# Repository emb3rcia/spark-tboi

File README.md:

# spark-tboi
# Navigation
- [About project](#about-project)
  - [Motivation for the project](#motivation-for-the-project)
  - [Humorous additions](#humorous-additions)
  - [Pin tables](#pin-tables)
  - [Development tools](#development-tools)
  - [Features](#features)
- [Images](#images)
- [License](#license)

# About project

spark-tboi is small-footprint keyboard/macropad with autoclicking capabilities and hot-swappable switches for The Binding of Isaac: Repentance+

## Motivation for the project

spark-debug was created to reduce strain on arms that happens when spam-clicking arrow keys with items such as Spirit Sword or Chocolate Milk

## Humorous additions

I added humorous silkscreen text as this project lacks personality without them in my opinion.

## Pin tables

Pin tables on PCB's silkscreen are named based on IC pins, not on desired connection on it. This means that TX UART pin should be plugged to RX of debugged device and vice versa.

## Usage

spark-tboi can run either only with firmware only or with integration with TBoI via mod that will be made after building the device.

## Directory overview

- 3D file of PCB and case files are available in `/3D`
- KiCad project files are available in `/KiCad Project Files`
- Gerber files are available in `/Gerbers`
- Firmware files are available in `/Firmware`

## Development tools

- KiCad for EDA work
- STM32CubeMX and CLion for firmware
- Fusion Educational Edition for CAD work

## Features

- Small footprint
- Autoclicking capabilities for specific items
- OLED screen

# Images

Schematic

3D viewer top side

3D viewer bottom side

Case assembled

Top plate

Bottom case

# License

## PCB / Schematic License

All files in `/PCB`, `/Schematic` and `/Gerbers` folders and their subsequent subfolders are licensed under the CERN Open Hardware License v2 (Weakly Reciprocal).

See `/Licenses/CERN-OHL.txt` for full terms.

## 3D files, images and documentation License

All files in `/3D`, `/Images` folders and their subsequent subfolders are licensed under the CC-BY 4.0 License.

See `/Licenses/CC-BY-4.0.txt` for full terms

## Software License

All files in `/Firmware` folder and their subsequent subfolders are licensed under the Apache 2.0 License.

See `/Licenses/Apache-2.0.txt` for full terms.

# BOM

|Name                          |Purpose                                                          |Quantity|Total Cost (USD)|Link                                                                                                 |Distributor|
|------------------------------|-----------------------------------------------------------------|--------|----------------|-----------------------------------------------------------------------------------------------------|-----------|
|GRM1555C1H180JA01D            |Capacitors for crystal                                           |2       |0.22            |https://www.tme.eu/pl/details/grm1555c1h180ja01d/kondensatory-mlcc-smd/murata/                       |TME        |
|0603B103K500CT                |Decoupling capacitors for MCU                                    |4       |0.27            |https://www.tme.eu/pl/en/details/0603b103k500ct/mlcc-smd-capacitors/walsin/                          |TME        |
|ABMM2-8.000MHZ-E2-T           |8 MHz oscillator for USB FS                                      |1       |1.03            |https://www.tme.eu/pl/en/details/abmm2-8.000mhz-e2/smd-quartz-generators/abracon/abmm2-8-000mhz-e2-t/|TME        |
|Outemu Kailh CPG151101S11     |Hot-swap switches (i have them from other project)               |15      |0.00            |https://pl.aliexpress.com/item/1005002637150446.html?gatewayAdapt=glo2pol                            |AliExpress |
|Switches and keycaps          |Physical buttons (i have them from hackpad kit and other project)|15      |0.00            |                                                                                                     |HackClub   |
|FOJAN FRC0603J472 TS          |Pull up/down resistors (i have them from other project)          |3       |0.00            |https://www.lcsc.com/product-detail/C2907166.html                                                    |LCSC       |
|Samsung Electro-Mechanics     |10uf decoupling capacitor (i have them from other project)       |1       |0.00            |https://www.lcsc.com/product-detail/C19702.html                                                      |LCSC       |
|HRE CGA0603X7R104K500JT       |100nf decoupling capacitors (i have them from other project)     |2       |0.00            |https://www.lcsc.com/product-detail/C6119867.html                                                    |LCSC       |
|Littelfuse SMBJ5.0A           |TVS diode for vbus (i have it from different project)            |1       |0.00            |https://www.lcsc.com/product-detail/C83333.html                                                      |LSCS       |
|Alps EC11                     |Rotary Encoder leftover from hackpad kit                         |1       |0.00            |                                                                                                     |HackClub   |
|SSD1306                       |OLED 128x32 SSD1306 screen leftover from hackpad kit             |1       |0.00            |                                                                                                     |HackClub   |
|SHOU HAN TYPE-C 16PIN 2MD(073)|USB-C Port (i have it from other project)                        |1       |0.00            |https://www.lcsc.com/product-detail/C2765186.html?s_z=n_C2765186                                     |LCSC       |
|PCB                           |PCB                                                              |5       |32.50           |https://jlcpcb.com                                                                                   |JLCPCB     |
|ST STM32F103C8T7              |MCU                                                              |1       |7.00            |https://www.tme.eu/pl/details/stm32f103c8t7/mikrokontrolery-st/stmicroelectronics/                   |TME        |

© 2026 emb3rcia

Hardware: CERN OHL v2
3D & Images: CC BY 4.0
Firmware: Apache 2.0

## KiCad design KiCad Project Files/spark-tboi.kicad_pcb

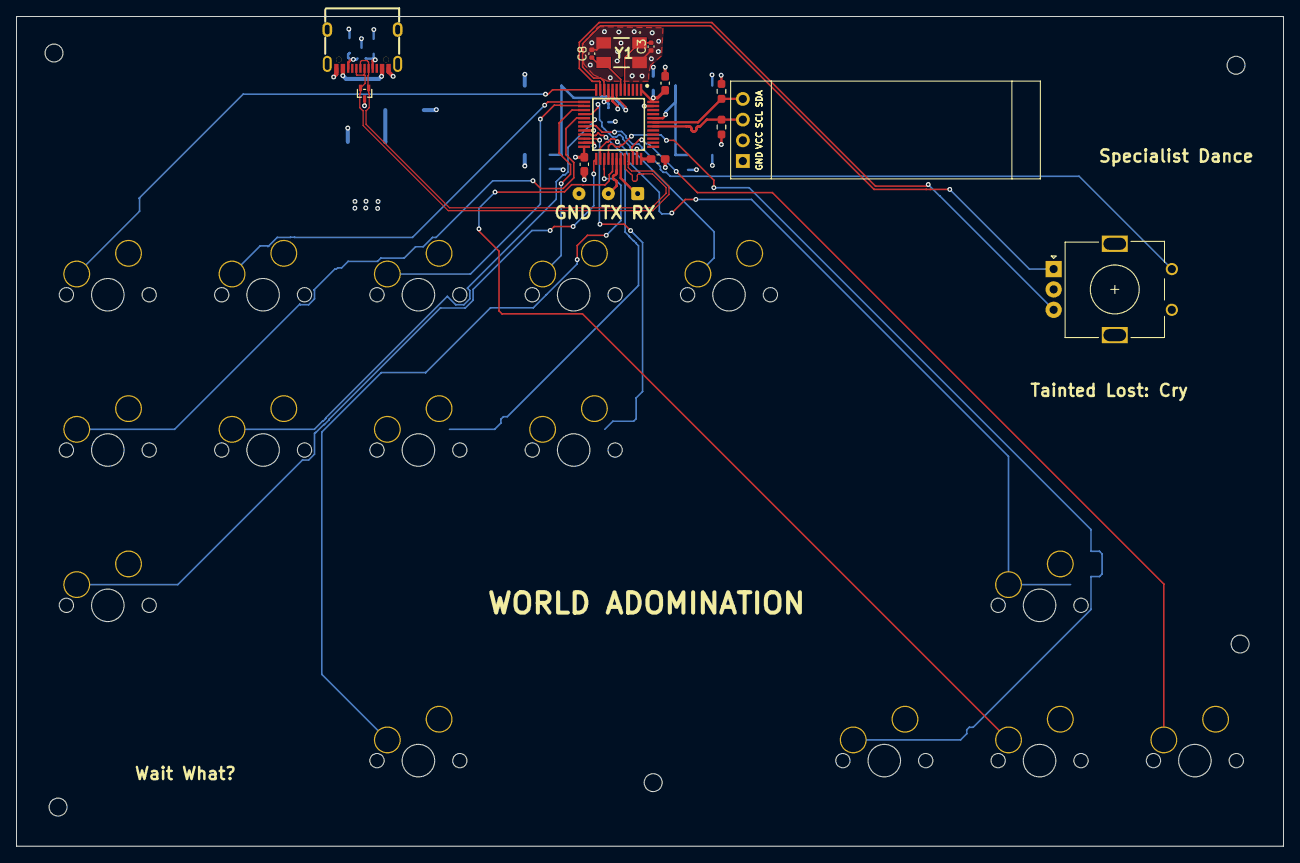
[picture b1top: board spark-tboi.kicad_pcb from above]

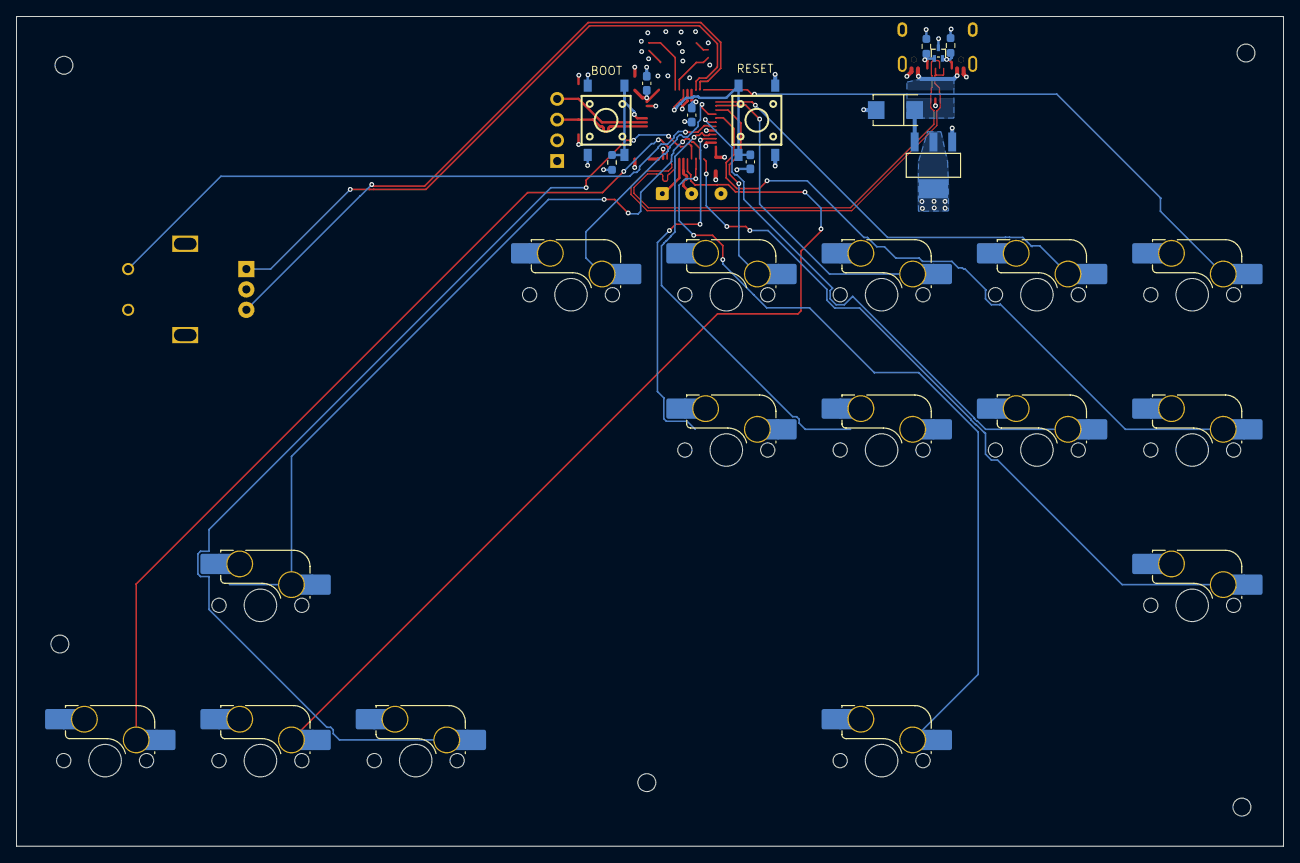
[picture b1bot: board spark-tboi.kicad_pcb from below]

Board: 4 copper layers, 155.4 x 101.8 mm, 40 parts (26 on the bottom side), 32 nets.

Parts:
3V3_LDO1: AMS1117-3.3_C917183; SOT-223-3_L6.7-W3.7-P2.30-LS7.0-BR
BOOT_BUTTON1: TS6643TP 250GF 009; SW-SMD_4P-L6.2-W6.0-P4.50-LS9.0
C1: 4.7uF; C_0603_1608Metric_Pad1.08x0.95mm_HandSolder
C2, C4, C6, C7: 10nF; C_0603_1608Metric_Pad1.08x0.95mm_HandSolder
C3, C8: 18pF; C_0402_1005Metric
C5: 100nF; C_0603_1608Metric_Pad1.08x0.95mm_HandSolder
CC_TVS1: RCLAMP0502BATCT; SC-75-3_L1.6-W0.8-P1.00-LS1.6-BR
CH1, CH2, CH3, CH4, CH5, CH6, CH7, CH8, CH9, CH10, CH11, CH12, CH13, CH14, CH15: KS33_SW_HS; SW_MX_HS_CPG151101S11_1u
DATA_TVS1: RCLAMP0502BATCT; SC-75-3_L1.6-W0.8-P1.00-LS1.6-BR
ENCODER1: RotaryEncoder_Switch; RotaryEncoder_Alps_EC11E_Vertical_H20mm
IC1: STM32F103C8T7; QFP50P900X900X160-48N
NRST_BUTTON1: TS6643TP 250GF 009; SW-SMD_4P-L6.2-W6.0-P4.50-LS9.0
OLED1: Conn_01x04_Pin; SSD1306-0.91-OLED-4pin-128x32
R1, R2, R3: 4.7kOhm; R_0603_1608Metric_Pad0.98x0.95mm_HandSolder
R4, R5: 5.1kOhm; R_0603_1608Metric_Pad0.98x0.95mm_HandSolder
UART1: Conn_01x03_Pin; SolderWire-0.1sqmm_1x03_P3.6mm_D0.4mm_OD1mm
USB1: TYPE-C 16PIN 2MD(073); USB-C-SMD_TYPE-C-6PIN-2MD-073
VBUS_TVS1: SMBJ5.0A_C83333; SMB_L4.6-W3.6-LS5.3-RD
Y1: ABMM2-8.000MHZ-E2-T; ABMM2

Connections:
5V: 3V3_LDO1.3 (VIN), USB1.2 (VBUS), USB1.11 (VBUS), VBUS_TVS1.1
+3.3V: 3V3_LDO1.2 (VOUT), 3V3_LDO1.4 (VOUT), BOOT_BUTTON1.3 (C), BOOT_BUTTON1.4 (D), C1.1, C2.1, C4.1, C6.1, C7.1, IC1.1 (VBAT), IC1.9 (VDDA), IC1.24 (VDD_1), IC1.36 (VDD_2), IC1.48 (VDD_3), OLED1.2, R1.1, R2.1
BOOT0: BOOT_BUTTON1.1 (A), BOOT_BUTTON1.2 (B), IC1.44 (BOOT0), R3.1
CC1: CC_TVS1.1, R5.1, USB1.4 (CC1)
CC2: CC_TVS1.2, R4.1, USB1.10 (CC2)
GND: 3V3_LDO1.1 (GND), C1.2, C2.2, C3.1, C4.2, C5.2, C6.2, C7.2, C8.2, CC_TVS1.3, CH1.2, CH2.2, CH3.2, CH4.2, CH5.2, CH6.2, CH7.2, CH8.2, CH9.2, CH10.2, CH11.2, CH12.2, CH13.2, CH14.2, CH15.2, DATA_TVS1.3, ENCODER1.C, IC1.8 (VSSA), IC1.20 (PB2), IC1.23 (VSS_1), IC1.35 (VSS_2), IC1.47 (VSS_3), NRST_BUTTON1.3 (C), NRST_BUTTON1.4 (D), OLED1.1, R3.2, R4.2, R5.2, UART1.3, USB1.1 (GND), USB1.12 (GND), USB1.13 (SHELL), USB1.14 (SHELL), VBUS_TVS1.2, Y1.2 (GND_1), Y1.4 (GND_2)
NRST: C5.1, IC1.7 (NRST), NRST_BUTTON1.1 (A), NRST_BUTTON1.2 (B)
unnamed: C3.2, IC1.5 (PD0-OSC_IN), Y1.1 (X1)
unnamed: C8.1, IC1.6 (PD1-OSC_OUT), Y1.3 (X2)
ROTARY_A: ENCODER1.A, IC1.10 (PA0-WKUP)
ROTARY_B: ENCODER1.B, IC1.11 (PA1)
SCL: IC1.42 (PB6), OLED1.3, R1.2
SDA: IC1.43 (PB7), OLED1.4, R2.2
SW1: CH1.1, IC1.12 (PA2)
SW2: CH2.1, IC1.13 (PA3)
SW3: CH3.1, IC1.14 (PA4)
SW4: CH4.1, IC1.15 (PA5)
SW5: CH5.1, IC1.16 (PA6)
SW6: CH6.1, IC1.17 (PA7)
SW7: CH7.1, IC1.18 (PB0)
SW8: CH8.1, IC1.21 (PB10)
SW9: CH9.1, IC1.22 (PB11)
SW10: CH10.1, IC1.25 (PB12)
SW11: CH11.1, IC1.26 (PB13)
SW12: CH12.1, IC1.27 (PB14)
SW13: CH13.1, IC1.28 (PB15)
SW14: CH14.1, IC1.29 (PA8)
SW15: CH15.1, IC1.34 (PA13)
UART_RX: IC1.31 (PA10), UART1.1
UART_TX: IC1.30 (PA9), UART1.2
USB_DN: DATA_TVS1.1, IC1.32 (PA11), USB1.5 (DN2), USB1.7 (DN1)
USB_DP: DATA_TVS1.2, IC1.33 (PA12), USB1.6 (DP1), USB1.8 (DP2)

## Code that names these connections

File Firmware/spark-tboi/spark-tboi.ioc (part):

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Mcu.Name=STM32F103C(8-B)Tx
Mcu.Package=LQFP48
Mcu.UserName=STM32F103C8Tx
PA0-WKUP.GPIOParameters=GPIO_Label
PA0-WKUP.GPIO_Label=ROTARY_A
PA0-WKUP.Signal=S_TIM2_CH1_ETR
PA1.GPIOParameters=GPIO_Label
PA1.GPIO_Label=ROTARY_B
PA1.Signal=S_TIM2_CH2
PA10.Mode=Asynchronous
PA10.Signal=USART1_RX
PA11.Mode=Device
PA11.Signal=USB_DM
PA12.Mode=Device
PA12.Signal=USB_DP
PA13.GPIOParameters=GPIO_PuPd,GPIO_Label
PA13.GPIO_Label=SW15
PA13.GPIO_PuPd=GPIO_PULLUP
PA13.Signal=GPIO_Input
PA2.GPIOParameters=GPIO_PuPd,GPIO_Label
PA2.GPIO_Label=SW1
PA2.GPIO_PuPd=GPIO_PULLUP
PA2.Signal=GPIO_Input
PA3.GPIOParameters=GPIO_PuPd,GPIO_Label
PA3.GPIO_Label=SW2
PA3.GPIO_PuPd=GPIO_PULLUP
PA3.Signal=GPIO_Input
PA4.GPIOParameters=GPIO_PuPd,GPIO_Label
PA4.GPIO_Label=SW3
PA4.GPIO_PuPd=GPIO_PULLUP
PA4.Signal=GPIO_Input
PA5.GPIOParameters=GPIO_PuPd,GPIO_Label
PA5.GPIO_Label=SW4
PA5.GPIO_PuPd=GPIO_PULLUP
PA5.Signal=GPIO_Input
PA6.GPIOParameters=GPIO_PuPd,GPIO_Label
PA6.GPIO_Label=SW5
PA6.GPIO_PuPd=GPIO_PULLUP
PA6.Signal=GPIO_Input
PA7.GPIOParameters=GPIO_PuPd,GPIO_Label
PA7.GPIO_Label=SW6
PA7.GPIO_PuPd=GPIO_PULLUP
PA7.Signal=GPIO_Input
PA8.GPIOParameters=GPIO_PuPd,GPIO_Label
PA8.GPIO_Label=SW14
PA8.GPIO_PuPd=GPIO_PULLUP
PA8.Signal=GPIO_Input
PA9.Mode=Asynchronous
PA9.Signal=USART1_TX
PB0.GPIOParameters=GPIO_PuPd,GPIO_Label
PB0.GPIO_Label=SW7
PB0.GPIO_PuPd=GPIO_PULLUP
PB0.Signal=GPIO_Input
PB1.GPIOParameters=GPIO_PuPd,GPIO_Label
PB1.GPIO_Label=ENCODER_SWITCH
PB1.GPIO_PuPd=GPIO_PULLUP
PB1.Signal=GPIO_Input
PB10.GPIOParameters=GPIO_PuPd,GPIO_Label
PB10.GPIO_Label=SW8
PB10.GPIO_PuPd=GPIO_PULLUP
PB10.Signal=GPIO_Input
PB11.GPIOParameters=GPIO_PuPd,GPIO_Label
PB11.GPIO_Label=SW9
PB11.GPIO_PuPd=GPIO_PULLUP
PB11.Signal=GPIO_Input
PB12.GPIOParameters=GPIO_PuPd,GPIO_Label
PB12.GPIO_Label=SW10
PB12.GPIO_PuPd=GPIO_PULLUP
PB12.Signal=GPIO_Input
PB13.GPIOParameters=GPIO_PuPd,GPIO_Label
PB13.GPIO_Label=SW11
PB13.GPIO_PuPd=GPIO_PULLUP
PB13.Signal=GPIO_Input
PB14.GPIOParameters=GPIO_PuPd,GPIO_Label
PB14.GPIO_Label=SW12
PB14.GPIO_PuPd=GPIO_PULLUP
PB14.Signal=GPIO_Input
PB15.GPIOParameters=GPIO_PuPd,GPIO_Label
PB15.GPIO_Label=SW13
PB15.GPIO_PuPd=GPIO_PULLUP
PB15.Signal=GPIO_Input
PB6.Mode=I2C
PB6.Signal=I2C1_SCL
PB7.Mode=I2C
PB7.Signal=I2C1_SDA
PD0-OSC_IN.Mode=HSE-External-Oscillator
PD0-OSC_IN.Signal=RCC_OSC_IN
PD1-OSC_OUT.Mode=HSE-External-Oscillator
PD1-OSC_OUT.Signal=RCC_OSC_OUT
RCC.SYSCLKFreq_VALUE=72000000
RCC.SYSCLKSource=RCC_SYSCLKSOURCE_PLLCLK
board=custom

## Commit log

2026-03-15 Push
2026-03-16 added case
2026-03-16 added images of case
2026-03-16 fixed bom
2026-03-16 Changed README.md
2026-03-17 revised bom
2026-03-21 Update README with 3d case image // need to add encoder cutout next
2026-03-23 Added extrusion for encoder
2026-04-08 Changed distributor to TME
